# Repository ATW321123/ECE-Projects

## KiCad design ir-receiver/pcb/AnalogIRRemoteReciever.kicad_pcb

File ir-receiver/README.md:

# Infrared Receiver Signal Chain

A discrete 38kHz IR Reciever, 4 fundamental analog stages followed by a fixed DSP decoder.

## Repository layout

| Folder | Contents |
|---|---|
| `pcb/` | KiCad 10 project (`.kicad_pro/.kicad_sch/.kicad_pcb`); `pcb/gerbers/` holds the fab outputs |
| `sim/` | Documented LTspice testbenches (Drafts 1-3) and `LM324.lib` |
| `sim/drafts/` | Working LTspice drafts 3-5: NEC-frame stimulus, ×10 gain stage, noise tests, DC servo |
| `sim/exports/` | Waveform exports the DSP scripts read (gitignored; re-export from `sim/drafts/`) |
| `DSP/` | Python + fixed-point C decoders (Goertzel, I/Q) that replace the comparator; see [`DSP/RESULTS.md`](DSP/RESULTS.md) |
| `docs/` | Figures used in this README |

## Signal chain

```
Photodiode → Transimpedance amp → 38 kHz bandpass → Comparator → Output conditioning
```

| Stage | Purpose |
|---|---|
| Transimpedance amplifier | Photodiode current to voltage, 330 kV/A (330 mV/µA) |
| Bandpass filter | 38 kHz center; rejects 120 Hz ambient-light interference |
| Comparator | Squares the recovered envelope to a logic level; Draft 3 adds about 100 mV of hysteresis (LT1011, 10 kΩ / 330 kΩ) |
| Output conditioning | Logic-level output for the ESP32 decoder: 660 Ω / 1 kΩ divider on the board, 4.7 kΩ pull-up to 3.3 V in Draft 3 |

## Schematic

<h3>Noise sources in the LTspice testbench</h3>

<p>Every source is a current source from VDD into the photodiode node, so it adds photocurrent
the way real light does. Voltages are the effect at the TIA output (× 330 kΩ).</p>

<table>
  <thead>
    <tr>
      <th>Part</th>
      <th>LTspice value</th>
      <th>What it models</th>
      <th>Size</th>
      <th>Effect at V(tia)</th>
    </tr>
  </thead>
  <tbody>
    <tr>
      <td><b>I1</b></td>
      <td><code>PWL file=..\..\DSP\nec_20nA.pwl</code></td>
      <td><b>The signal:</b> NEC remote frame, 38 kHz carrier at 1/3 duty</td>
      <td>20 nA pulses</td>
      <td>~6.6 mV pulses (carrier ≈ 4.5 ADC codes)</td>
    </tr>
    <tr>
      <td><b>I2</b></td>
      <td><code>1µ</code></td>
      <td>Steady room light / daylight</td>
      <td>1 µA DC</td>
      <td>−0.33 V shift</td>
    </tr>
    <tr>
      <td><b>I3</b></td>
      <td><code>SINE(2u 1u 120)</code></td>
      <td>Mains lamp flicker at 120 Hz (twice the 60 Hz mains)</td>
      <td>2 µA average ± 1 µA</td>
      <td>−0.66 V shift, ±0.33 V ripple (±410 codes)</td>
    </tr>
    <tr>
      <td><b>I4</b></td>
      <td><code>SINE(100n 100n 45k)</code></td>
      <td>Interfering IR at 45 kHz (CFL / electronic-ballast lamp)</td>
      <td>0–200 nA (100 nA average + 100 nA swing)</td>
      <td>−33 mV shift, ±33 mV (±41 codes)</td>
    </tr>
    <tr>
      <td><b>B1</b></td>
      <td><code>I=5n*white(1e6*time)</code></td>
      <td>Broadband random noise (stand-in for shot and amplifier noise), new value every 1 µs</td>
      <td>±2.5 nA uniform, ≈ 1.4 nA rms</td>
      <td>≈ 0.5 mV rms</td>
    </tr>
  </tbody>
</table>

<p>Also on the photodiode node, but part of the diode model rather than noise:
<b>R1 = 10 MΩ</b> (shunt leakage) and <b>C3 = 20 pF</b> (junction capacitance, which sets the TIA's
stability and bandwidth together with C4 = 4.7 pF).</p>

<p>Total average light is about 3 µA, so V(tia) sits near 2.5 − 0.99 ≈ 1.5 V (simulated
1.02–1.75 V), well clear of TIA saturation at about 7.5 µA. LTspice transient analysis has no
built-in device noise (resistor, op-amp or photodiode shot noise); B1 stands in for it.</p>

<h4>Variants (<code>sim/drafts/</code>)</h4>

<table>
  <thead>
    <tr>
      <th>File</th>
      <th>Change from the all-noises testbench</th>
    </tr>
  </thead>
  <tbody>
    <tr><td><code>Draft6_int60k.asc</code></td><td>I4 → <code>SINE(100n 100n 60k)</code></td></tr>
    <tr><td><code>Draft6_int100k.asc</code></td><td>I4 → <code>SINE(100n 100n 100k)</code></td></tr>
    <tr><td><code>Draft6_flicker60.asc</code></td><td>I3 → <code>SINE(2u 1u 60)</code></td></tr>
    <tr><td><code>Draft6_flicker100.asc</code></td><td>I3 → <code>SINE(2u 1u 100)</code></td></tr>
    <tr><td><code>Draft6_no45k.asc</code></td><td>I4 → <code>0</code></td></tr>
    <tr><td><code>Draft6_clean.asc</code></td><td>I2, I3, I4 → <code>0</code>; B1 → <code>I=0</code> (20 nA remote only)</td></tr>
  </tbody>
</table>

## Sim Results

The Bandpass filter's gain (Vbf/Vtia), where Vtia is the voltage signal from the transimpedance amplifer effectively adds ~14.7 dB of gain at 37.6kHz. Other signals from the noise simulations all have less gain except for the 45kHz lamp signal. This explains why the pure analog to comparator chain is not sufficient in isolating the 38kHz, since the 45kHz signal is too near it.

Different simulations running assuming a 38kHz signal strength of 20nA from photodiode. With no interference from other sources, the comparator decodes the frame cleanly. Adding room lights, flickers, and noise did not break it either. A 45kHz source however does and passes through the analog bandpass filter along with the 38kHz remote signal and results in a failure to decode.
Results from the final 'out' node given just the comparator.

## Goertzel Algorithm Implementation

If instead, connect the a microcontroller directly after the bandpass filter and use the microcontroller to apply the DFT to isolate the 38kHz signal using the Goertzel algorithm, it is achievable to decode the signal w/o any comparator subcircuit. 

fs = 500kSPS (min 2 x 38kHz)
N = 128
fr = 4kHz
Hop = 32
Bin = 9.73

The combination of the bandpassfilter and Goertzel implementation coorelating last N number of samples with 38kHz reference and reports amplitude every 64µs. 38kHz component adds up while other frequencies are averaged towards zero. The adaptive slice functions as a way to turn the signal on and off by adjusting the threshold in accordance with the formula:

### How the receiver decides "on" or "off" (adaptive threshold)

The detector outputs a number every 64 µs: how strong the 38 kHz signal is right now.
To turn that into on/off, the receiver compares it to a threshold that **adjusts itself**.

It keeps track of two levels:

- **Quiet level (floor):** how strong the signal reads when the remote is *not* sending,
  i.e. background noise. It updates slowly (over about 20 ms) and only while nothing is being received.
- **Loud level (peak):** how strong the signal reads when the remote *is* sending. It jumps up
  immediately when a burst arrives and fades slowly (over about 150 ms) afterwards.

$$
\text{threshold} = F + k\,(P - F), \qquad
k = \begin{cases} 0.50 & \text{output off} \\ 0.35 & \text{output on} \end{cases}
$$

where **F** is the quiet level (floor) and **P** the loud level (peak). The output turns on
when the Goertzel amplitude exceeds the threshold **and** $P > 4F$.
The threshold sits between the two:

    threshold = quiet level + 50% of the gap between quiet and loud

Once the output switches on, the threshold drops to **35%** of the gap. It switches back
off only when the signal falls clearly below the level that turned it on, so small wobbles
near the line can't make it flicker on/off/on.

**Why adaptive?** A remote across the room gives a much weaker signal than one up close,
and a noisy room raises the quiet level. A fixed threshold would be wrong in one case or
the other. Tracking the quiet and loud levels keeps the threshold halfway between them,
whatever they are. Commercial IR receiver chips do the same thing with automatic gain control.

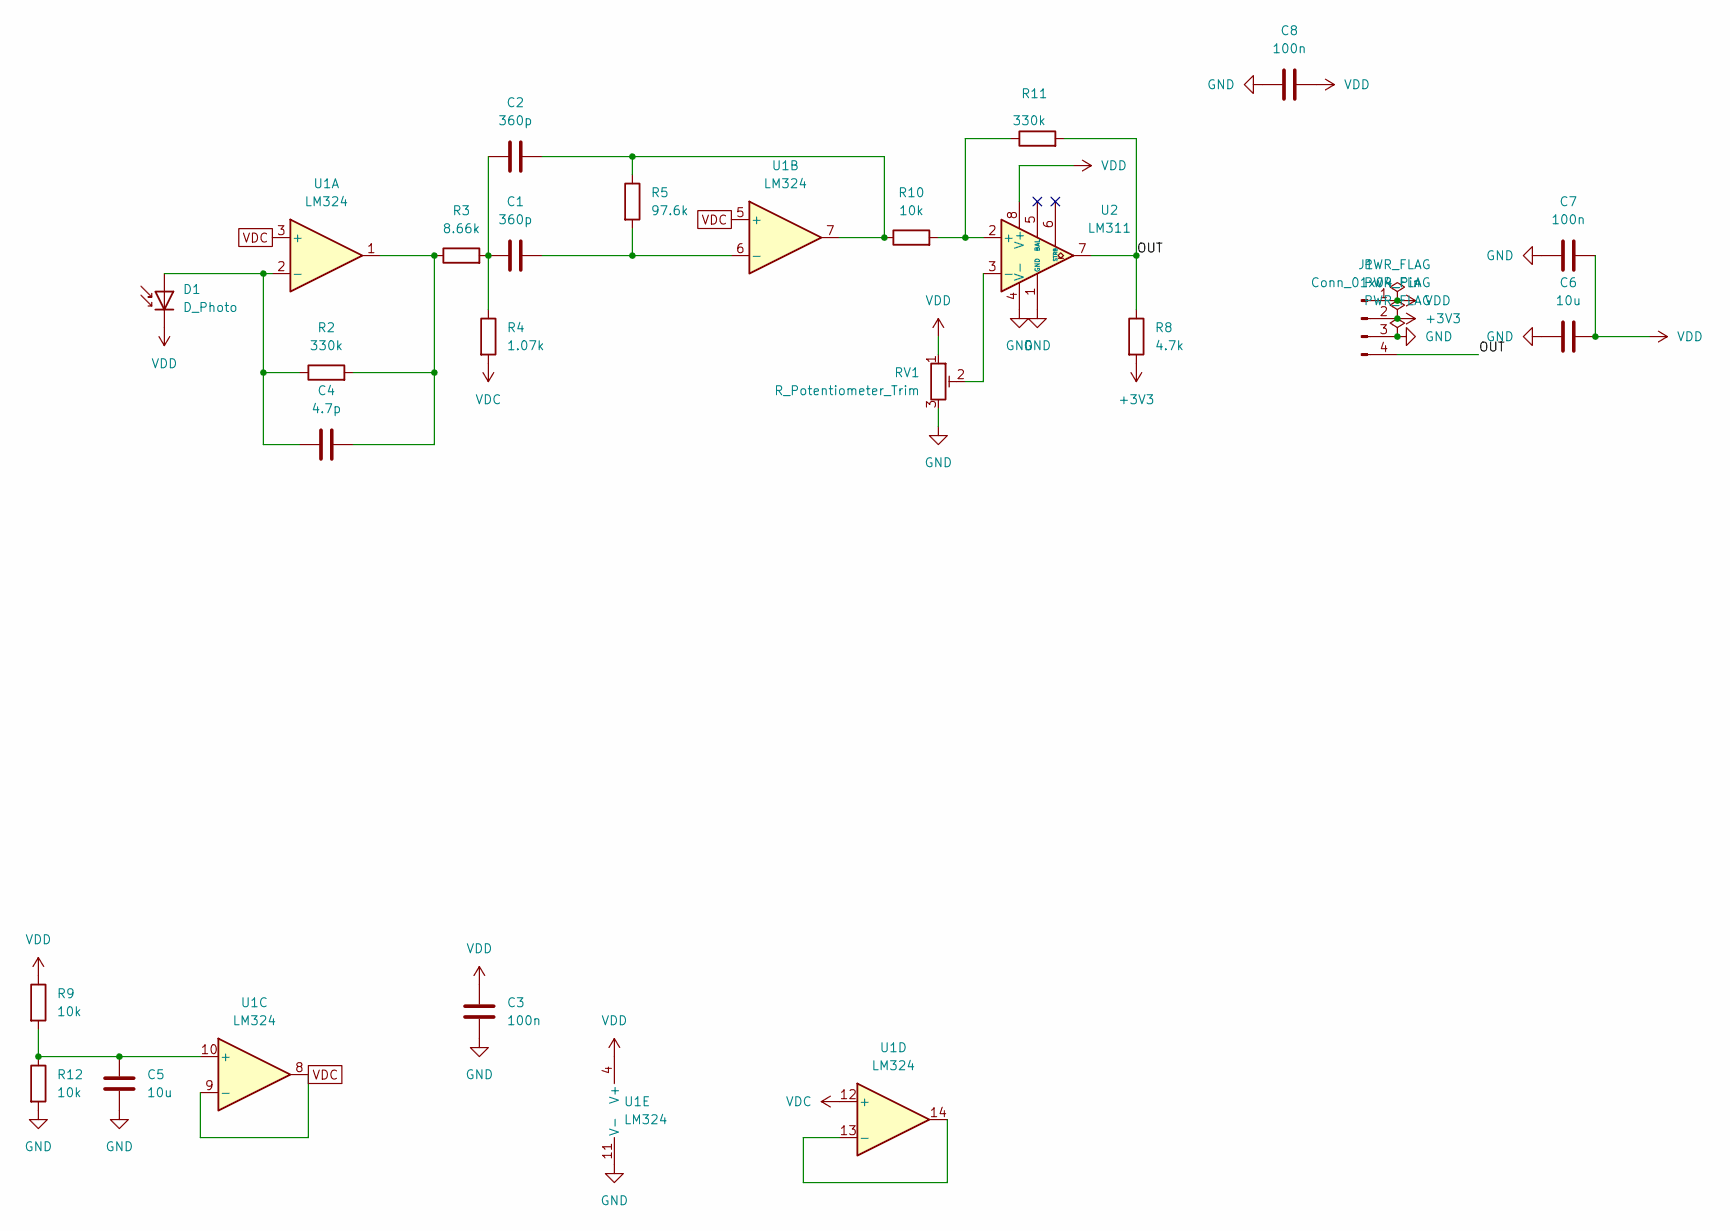
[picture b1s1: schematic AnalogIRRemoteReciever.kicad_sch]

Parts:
C1, C2: 360p; C_0805_2012Metric
C3, C7, C8: 100n; C_0805_2012Metric
C4: 4.7p; C_0805_2012Metric
C5, C6: 10u; C_0805_2012Metric
D1: D_Photo; Osram_DIL2_4.3x4.65mm_P5.08mm
J1: Conn_01x04_Pin; PinHeader_1x04_P2.54mm_Vertical
R2, R11: 330k; R_0805_2012Metric
R3: 8.66k; R_0805_2012Metric
R4: 1.07k; R_0805_2012Metric
R5: 97.6k; R_0805_2012Metric
R8: 4.7k; R_0805_2012Metric
R9, R10, R12: 10k; R_0805_2012Metric
RV1: R_Potentiometer_Trim; Potentiometer_Bourns_3296W_Vertical
U1: LM324; SOIC-14_3.9x8.7mm_P1.27mm
U2: LM311; SOIC-8_3.9x4.9mm_P1.27mm

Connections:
+3V3: J1.2, R8.2
/OUT: J1.4, R8.1, R11.2, U2.7
GND: C3.2, C5.2, C6.1, C7.1, C8.1, J1.3, R12.2, RV1.3, U1.11 (V-), U2.1 (GND), U2.4 (V-)
unnamed: C1.1, C2.1, R3.2, R4.1
unnamed: C2.2, R5.1, R10.1, U1.7
unnamed: C4.2, R2.2, R3.1, U1.1
unnamed: C4.1, D1.2 (A), R2.1, U1.2 (-)
unnamed: C1.2, R5.2, U1.6 (-)
unnamed: C5.1, R9.2, R12.1, U1.10 (+)
unnamed: U1.13 (-), U1.14
unnamed: R10.2, R11.1, U2.2 (+)
unnamed: RV1.2, U2.3 (-)
VDC: R4.2, U1.3 (+), U1.5 (+), U1.8, U1.9 (-), U1.12 (+)
VDD: C3.1, C6.2, C7.2, C8.2, D1.1 (K), J1.1, R9.1, RV1.1, U1.4 (V+), U2.8 (V+)

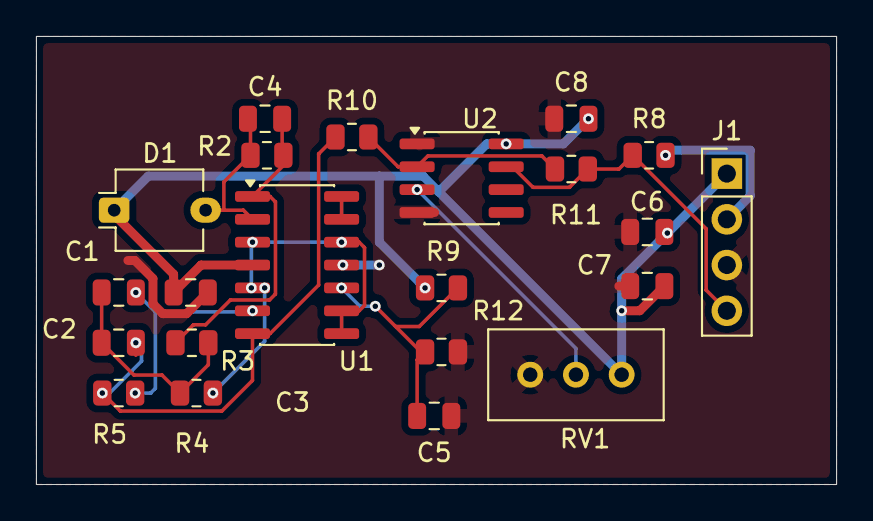
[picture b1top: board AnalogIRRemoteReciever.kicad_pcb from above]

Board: 2 copper layers, 44.5 x 24.9 mm, 22 parts (0 on the bottom side), 14 nets.
